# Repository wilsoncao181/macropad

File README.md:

# Macropad

I couldnt think of a better name :(

My hack pad has 5 buttons and a rotary encoder and uses qmk firmware. 

I just wanted to learn something new and this has been a very fun experience.

## Features

Very simple sandwich mount case with a 4 ish degree tilt!

Buttons will copy, paste, cut, undo and redo.

Rotary encoder will mute when clicked and turning it controls volume

## CAD model
Held together by 4 M3x20mm bolts, one in each corner of the case. It has 3 printed piece. 

The case which houses the pcb and has a cutout for the USB, and the plate which the keys will sit ontop of.

The screws will be screwed from the bottom and will go through 2mm of the tilted plate, 16mm of the main body and 2mm of the top plate. The bottom of the the tilted plate has holes to allow the entire screw (including the head) to travel through.

The third picture shows that I have left space for the headers which will connect the XIAO and the PCB. 

Made in fusion 360

## PCB
My PCB was made in KiCad 9.0.

Schematic:

PCB:

## Firmware
I used QMK firmware for it. (It took me way too long)
The rotary encoder changes volume and presses to mute
The 5 keys will:

-copy, 

-paste, 

-cut,

-undo and 

-redo.

## BOM
So to make this you'll need:

-5x Cherry MX Switches

-5x DSA Keycaps

-4x M3 x 20mm Full Thread Socket Cap Head Screws

-1x EC11 Rotary Encoder

-1x XIAO RP2040 + headers (to attach to PCB)

-1x Case (3 printed parts)

Thats it!

Anyways have a good day

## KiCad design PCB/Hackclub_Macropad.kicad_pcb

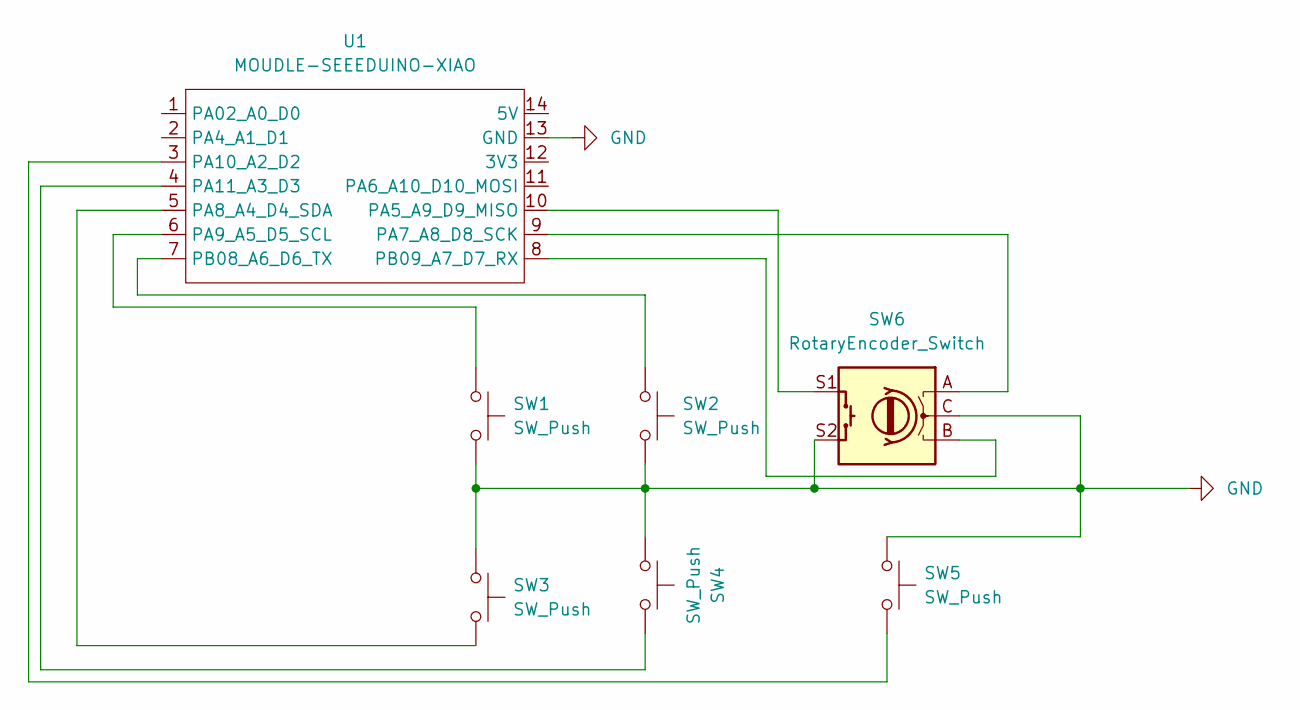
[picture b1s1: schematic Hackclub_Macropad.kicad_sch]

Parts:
SW1, SW2, SW3, SW4, SW5: SW_Push; SW_Cherry_MX_1.00u_PCB
SW6: RotaryEncoder_Switch; RotaryEncoder_Alps_EC11E-Switch_Vertical_H20mm
U1: MOUDLE-SEEEDUINO-XIAO; XIAO-Generic-Hybrid-14P-2.54-21X17.8MM

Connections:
GND: SW1.2, SW2.2, SW3.1, SW4.1, SW5.1, SW6.C, SW6.S2, U1.13 (GND)
unnamed: SW6.S1, U1.10 (PA5_A9_D9_MISO)
unnamed: SW6.A, U1.9 (PA7_A8_D8_SCK)
unnamed: SW3.2, U1.5 (PA8_A4_D4_SDA)
unnamed: SW1.1, U1.6 (PA9_A5_D5_SCL)
unnamed: SW5.2, U1.3 (PA10_A2_D2)
unnamed: SW4.2, U1.4 (PA11_A3_D3)
unnamed: SW2.1, U1.7 (PB08_A6_D6_TX)
unnamed: SW6.B, U1.8 (PB09_A7_D7_RX)

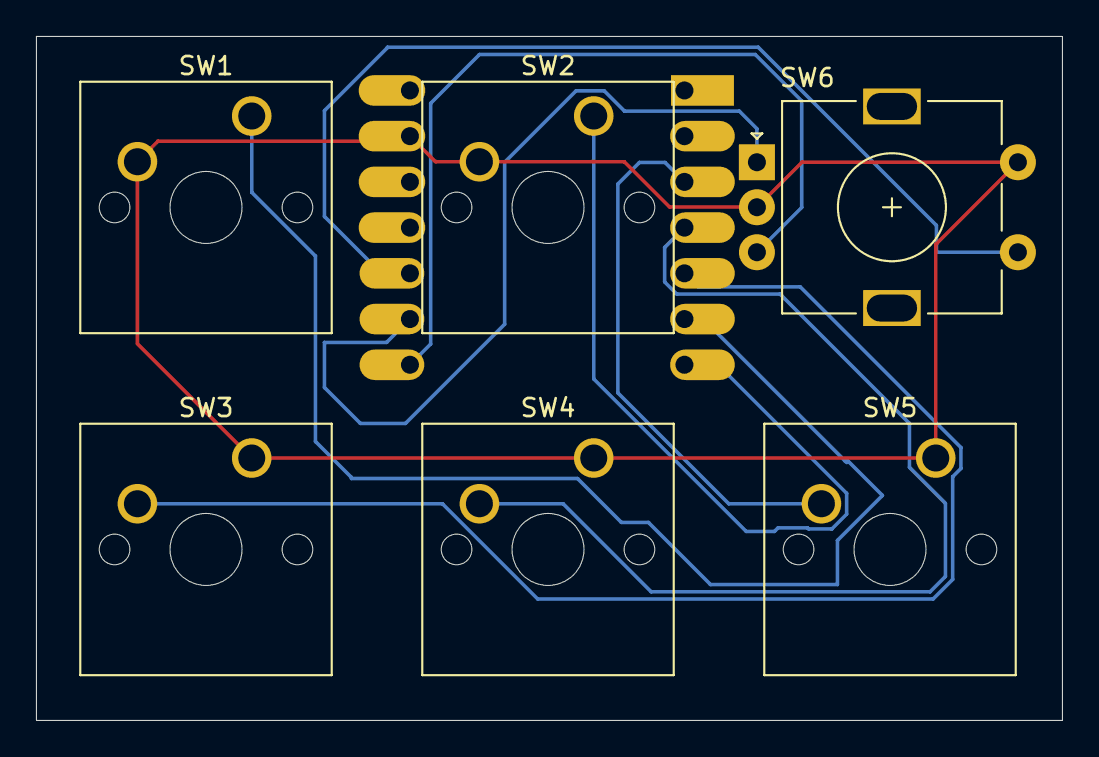
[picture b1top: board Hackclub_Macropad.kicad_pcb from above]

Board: 2 copper layers, 57.0 x 38.0 mm, 7 parts (1 on the bottom side), 9 nets.

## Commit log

2026-03-15 Create cad
2026-03-15 Rename HackPad.step to CAD/HackPad.step
2026-03-15 Rename Hackclub_Macropad.kicad_pcb to PCB/Hackclub_Macropad.kicad_pcb
2026-03-15 Rename Hackclub_Macropad.kicad_pro to PCB/Hackclub_Macropad.kicad_pro
2026-03-15 Rename Hackclub_Macropad.kicad_sch to PCB/Hackclub_Macropad.kicad_sch
2026-03-15 Rename readme.md to Firmware/README.md
2026-03-15 Rename keyboard.json to Firmware/keyboard.json
2026-03-15 Rename rules.mk to Firmware/rules.mk
2026-03-15 Rename gerbers.zip to Production/gerbers.zip
2026-03-15 Rename hackclub_macropad_default.uf2 to firmware.uf2
2026-03-15 Rename Bottom Case.png to Bottom_Case.png
2026-03-15 Rename Top Plate.png to Top_Plate.png
